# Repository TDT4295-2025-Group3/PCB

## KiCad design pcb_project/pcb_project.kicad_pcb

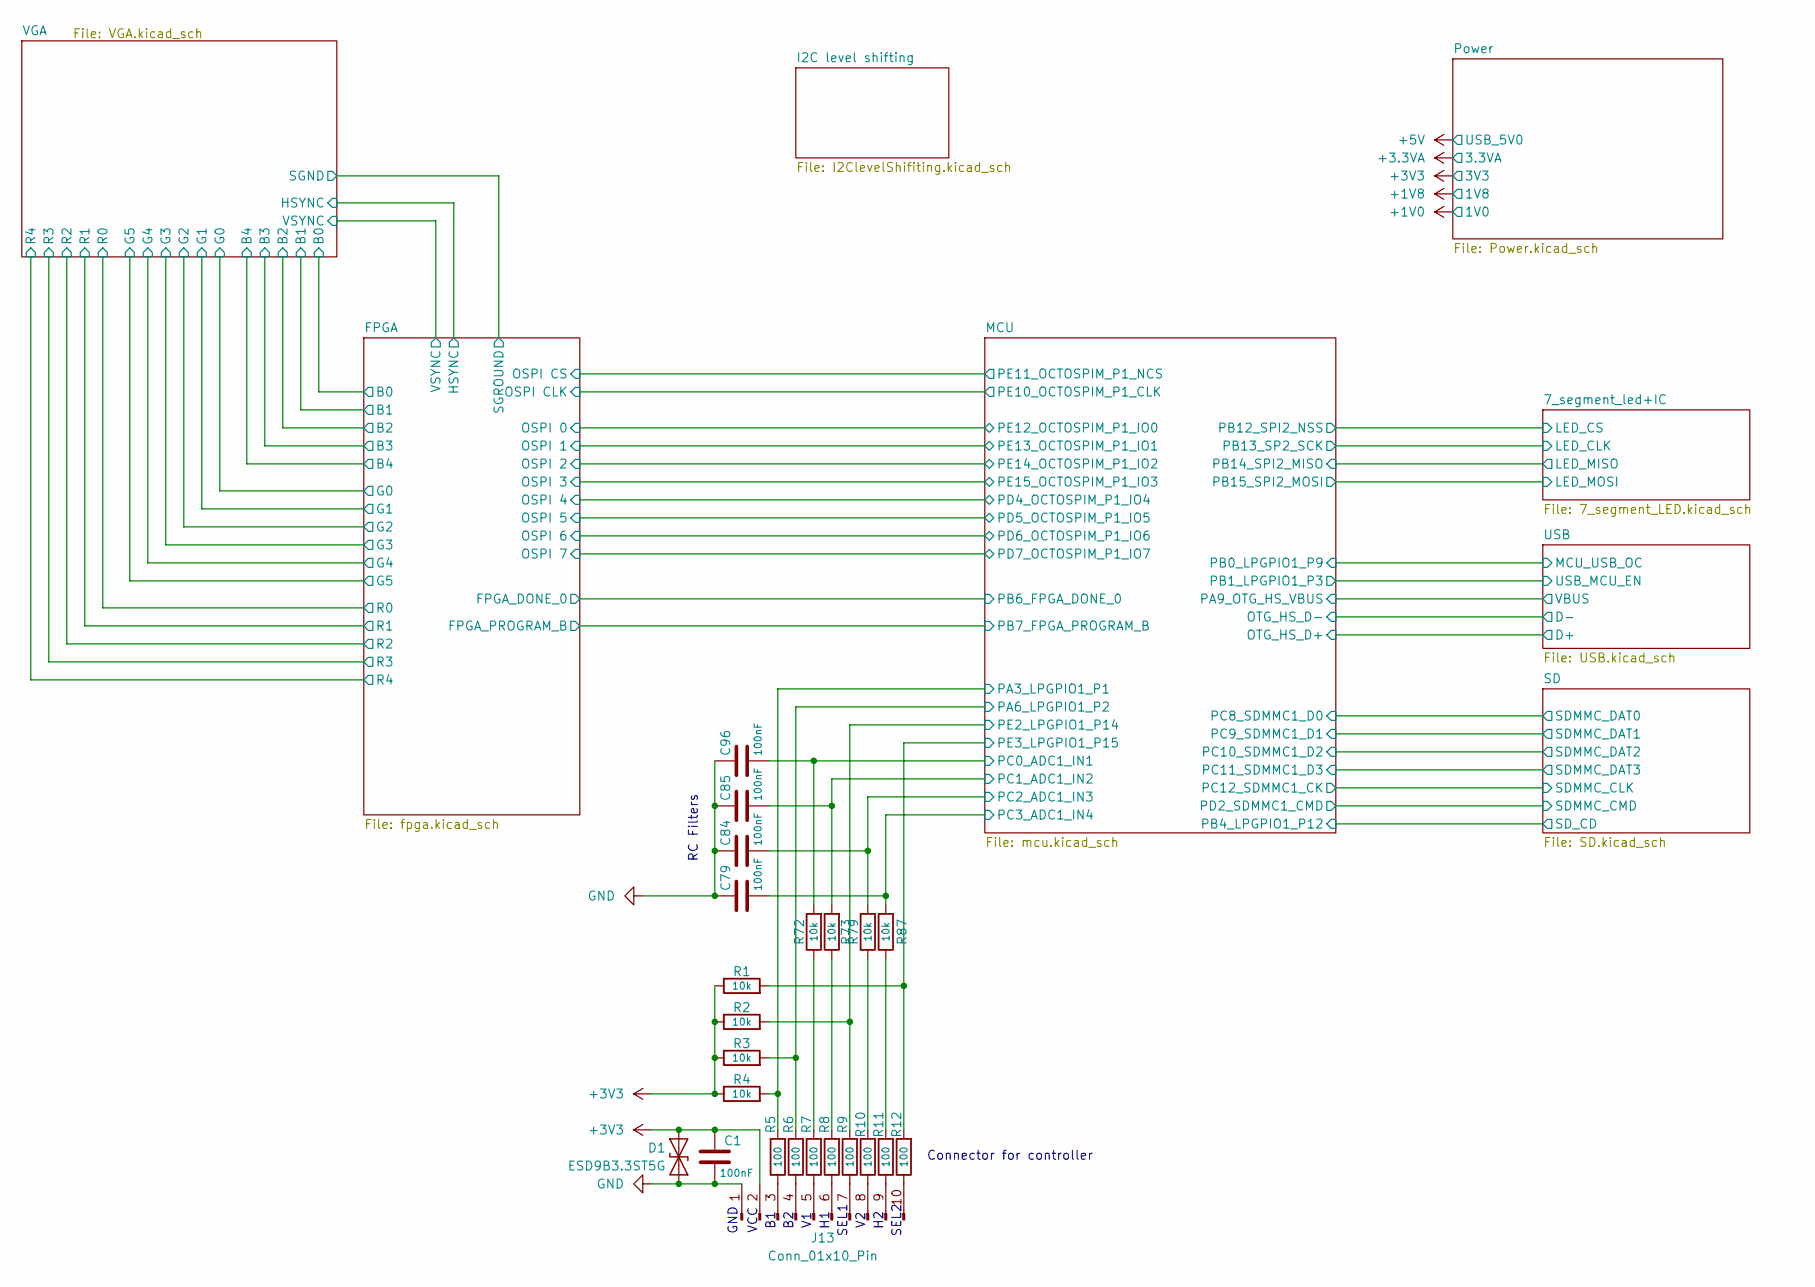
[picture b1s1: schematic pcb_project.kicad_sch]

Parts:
C1, C79, C84, C85, C96: 100nF; C_0603_1608Metric_Pad1.08x0.95mm_HandSolder
D1: ESD9B3.3ST5G; D_SOD-923
J13: Conn_01x10_Pin; PinHeader_1x10_P2.54mm_Vertical
R1, R2, R3, R4, R72, R73, R79, R87: 10k; R_0805_2012Metric_Pad1.20x1.40mm_HandSolder
R5, R6, R7, R8, R9, R10, R11, R12: 100; R_0805_2012Metric_Pad1.20x1.40mm_HandSolder

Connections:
+3V3: C1.1, D1.1 (A1), J13.2, R1.1, R2.1, R3.1, R4.1; also elsewhere on the board
/MCU/PA3_LPGPIO1_P1: R4.2, R5.2; also elsewhere on the board
/MCU/PA6_LPGPIO1_P2: R3.2, R6.2; also elsewhere on the board
/MCU/PC0_ADC1_IN1: C96.2, R72.2; also elsewhere on the board
/MCU/PC1_ADC1_IN2: C85.2, R73.2; also elsewhere on the board
/MCU/PC2_ADC1_IN3: C84.2, R79.2; also elsewhere on the board
/MCU/PC3_ADC1_IN4: C79.2, R87.2; also elsewhere on the board
/MCU/PE2_LPGPIO1_P14: R2.2, R9.2; also elsewhere on the board
/MCU/PE3_LPGPIO1_P15: R1.2, R12.2; also elsewhere on the board
GND: C1.2, C79.1, C84.1, C85.1, C96.1, D1.2 (A2), J13.1; also elsewhere on the board
unnamed: J13.3, R5.1
unnamed: J13.4, R6.1
unnamed: J13.5, R7.1
unnamed: J13.6, R8.1
unnamed: J13.7, R9.1
unnamed: J13.8, R10.1
unnamed: J13.9, R11.1
unnamed: J13.10, R12.1
unnamed: R7.2, R72.1
unnamed: R10.2, R79.1
unnamed: R11.2, R87.1
unnamed: R8.2, R73.1

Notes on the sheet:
VCC
SEL1
SEL2
Connector for controller
RC Filters
GND

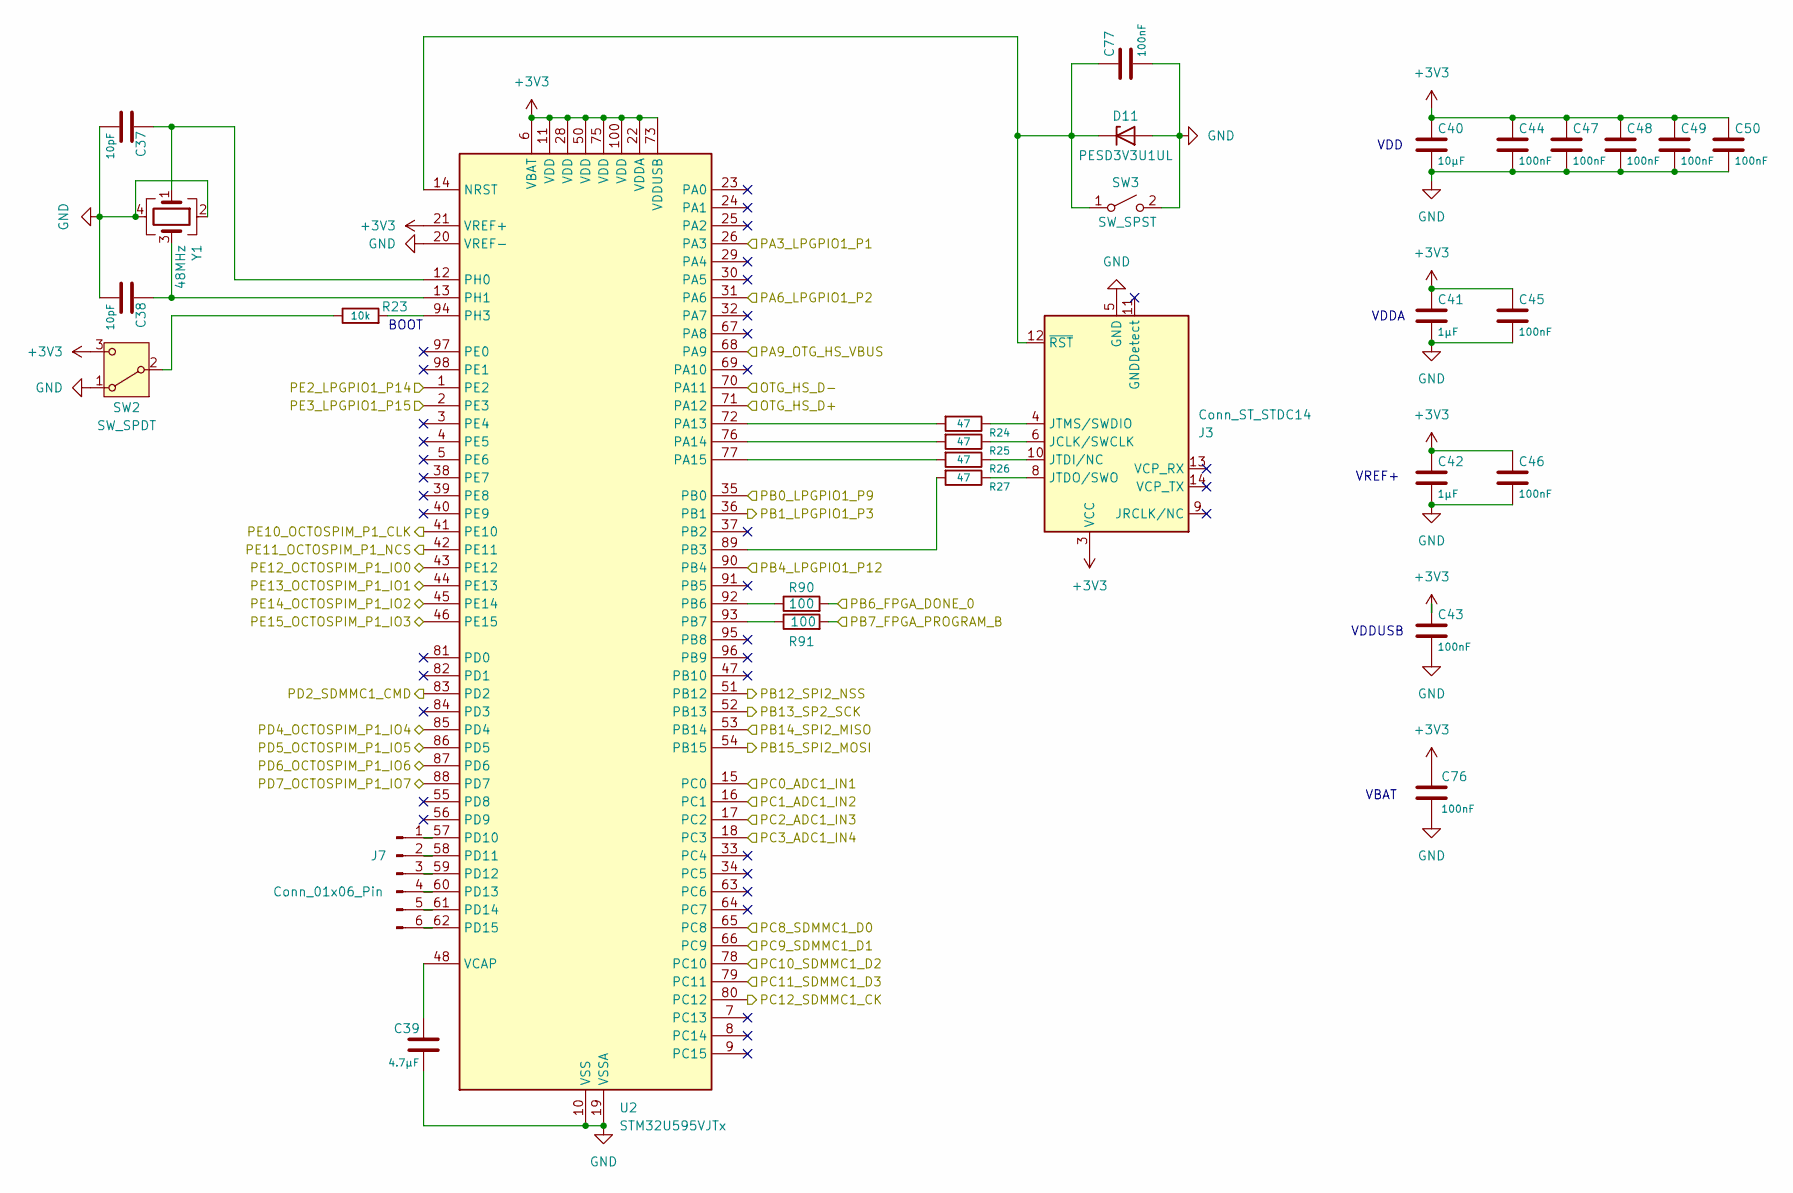
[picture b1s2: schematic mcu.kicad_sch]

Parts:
C37, C38: 10pF; C_0603_1608Metric_Pad1.08x0.95mm_HandSolder
C39: 4.7μF; C_0805_2012Metric_Pad1.18x1.45mm_HandSolder
C40: 10μF; C_1206_3216Metric_Pad1.33x1.80mm_HandSolder
C41, C42: 1μF; C_0805_2012Metric_Pad1.18x1.45mm_HandSolder
C43, C44, C45, C46, C47, C48, C49, C50, C76, C77: 100nF; C_0603_1608Metric_Pad1.08x0.95mm_HandSolder
D11: PESD3V3U1UL; D_SOD-882
J3: Conn_ST_STDC14; PinHeader_2x07_P1.27mm_Vertical
J7: Conn_01x06_Pin; PinHeader_1x06_P2.54mm_Vertical
R23: 10k; R_0805_2012Metric_Pad1.20x1.40mm_HandSolder
R24, R25, R26, R27: 47; R_0805_2012Metric_Pad1.20x1.40mm_HandSolder
R90, R91: 100; R_0805_2012Metric_Pad1.20x1.40mm_HandSolder
SW2: SW_SPDT; SW_Slide_SPDT_Straight_CK_OS102011MS2Q
SW3: SW_SPST; SW_TH_Tactile_Omron_B3F-100x
U2: STM32U595VJTx; LQFP-100_14x14mm_P0.5mm
Y1: 48MHz; OSCCC320X250X60N

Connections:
+3V3: C40.1, C41.1, C42.1, C43.1, C44.1, C45.1, C46.1, C47.1, C48.1, C49.1, C50.1, C76.1, J3.3 (VCC), SW2.3 (C), U2.6 (VBAT), U2.11 (VDD), U2.21 (VREF+), U2.22 (VDDA), U2.28 (VDD), U2.50 (VDD), U2.73 (VDDUSB), U2.75 (VDD), U2.100 (VDD); also elsewhere on the board
/7_segment_led+IC/LED_CLK: U2.52 (PB13); also elsewhere on the board
/7_segment_led+IC/LED_CS: U2.51 (PB12); also elsewhere on the board
/7_segment_led+IC/LED_MISO: U2.53 (PB14); also elsewhere on the board
/7_segment_led+IC/LED_MOSI: U2.54 (PB15); also elsewhere on the board
/FPGA/FPGA_DONE_0: R90.2; also elsewhere on the board
/FPGA/FPGA_PROGRAM_B: R91.2; also elsewhere on the board
/FPGA/OSPI 0: U2.43 (PE12); also elsewhere on the board
/FPGA/OSPI 1: U2.44 (PE13); also elsewhere on the board
/FPGA/OSPI 2: U2.45 (PE14); also elsewhere on the board
/FPGA/OSPI 3: U2.46 (PE15); also elsewhere on the board
/FPGA/OSPI 4: U2.85 (PD4); also elsewhere on the board
/FPGA/OSPI 5: U2.86 (PD5); also elsewhere on the board
/FPGA/OSPI 6: U2.87 (PD6); also elsewhere on the board
/FPGA/OSPI 7: U2.88 (PD7); also elsewhere on the board
/FPGA/OSPI CLK: U2.41 (PE10); also elsewhere on the board
/FPGA/OSPI CS: U2.42 (PE11); also elsewhere on the board
/MCU/OTG_HS_D+: U2.71 (PA12); also elsewhere on the board
/MCU/OTG_HS_D-: U2.70 (PA11); also elsewhere on the board
/MCU/PA3_LPGPIO1_P1: U2.26 (PA3); also elsewhere on the board
/MCU/PA6_LPGPIO1_P2: U2.31 (PA6); also elsewhere on the board
/MCU/PA9_OTG_HS_VBUS: U2.68 (PA9); also elsewhere on the board
/MCU/PB0_LPGPIO1_P9: U2.35 (PB0); also elsewhere on the board
/MCU/PB1_LPGPIO1_P3: U2.36 (PB1); also elsewhere on the board
/MCU/PB4_LPGPIO1_P12: U2.90 (PB4); also elsewhere on the board
/MCU/PC0_ADC1_IN1: U2.15 (PC0); also elsewhere on the board
/MCU/PC1_ADC1_IN2: U2.16 (PC1); also elsewhere on the board
/MCU/PC2_ADC1_IN3: U2.17 (PC2); also elsewhere on the board
/MCU/PC3_ADC1_IN4: U2.18 (PC3); also elsewhere on the board
/MCU/PC8_SDMMC1_D0: U2.65 (PC8); also elsewhere on the board
/MCU/PC9_SDMMC1_D1: U2.66 (PC9); also elsewhere on the board
/MCU/PC10_SDMMC1_D2: U2.78 (PC10); also elsewhere on the board
/MCU/PC11_SDMMC1_D3: U2.79 (PC11); also elsewhere on the board
/MCU/PC12_SDMMC1_CK: U2.80 (PC12); also elsewhere on the board
/MCU/PD2_SDMMC1_CMD: U2.83 (PD2); also elsewhere on the board
/MCU/PE2_LPGPIO1_P14: U2.1 (PE2); also elsewhere on the board
/MCU/PE3_LPGPIO1_P15: U2.2 (PE3); also elsewhere on the board
GND: C37.2, C38.2, C39.2, C40.2, C41.2, C42.2, C43.2, C44.2, C45.2, C46.2, C47.2, C48.2, C49.2, C50.2, C76.2, C77.2, D11.2 (A), J3.5 (GND), J3.7 (GND), SW2.1 (A), SW3.2 (B), U2.10 (VSS), U2.19 (VSSA), U2.20 (VREF-), U2.27 (VSS), U2.49 (VSS), U2.74 (VSS), U2.99 (VSS), Y1.2, Y1.4; also elsewhere on the board
unnamed: C77.1, D11.1 (K), J3.12 (~RST), SW3.1 (A), U2.14 (NRST)
unnamed: J3.6 (JCLK/SWCLK), R25.1
unnamed: J3.10 (JTDI/NC), R26.1
unnamed: J3.8 (JTDO/SWO), R27.1
unnamed: J3.4 (JTMS/SWDIO), R24.1
unnamed: J7.1, U2.57 (PD10)
unnamed: J7.2, U2.58 (PD11)
unnamed: J7.3, U2.59 (PD12)
unnamed: J7.4, U2.60 (PD13)
unnamed: J7.5, U2.61 (PD14)
unnamed: J7.6, U2.62 (PD15)
unnamed: R23.1, SW2.2 (B)
unnamed: R24.2, U2.72 (PA13)
unnamed: R25.2, U2.76 (PA14)
unnamed: R26.2, U2.77 (PA15)
unnamed: R27.2, U2.89 (PB3)
unnamed: R90.1, U2.92 (PB6)
unnamed: R91.1, U2.93 (PB7)
unnamed: C37.1, U2.12 (PH0), Y1.1
unnamed: C38.1, U2.13 (PH1), Y1.3
unnamed: R23.2, U2.94 (PH3)
unnamed: C39.1, U2.48 (VCAP)

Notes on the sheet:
VDD
BOOT
VDDA
VBAT
VDDUSB
VREF+

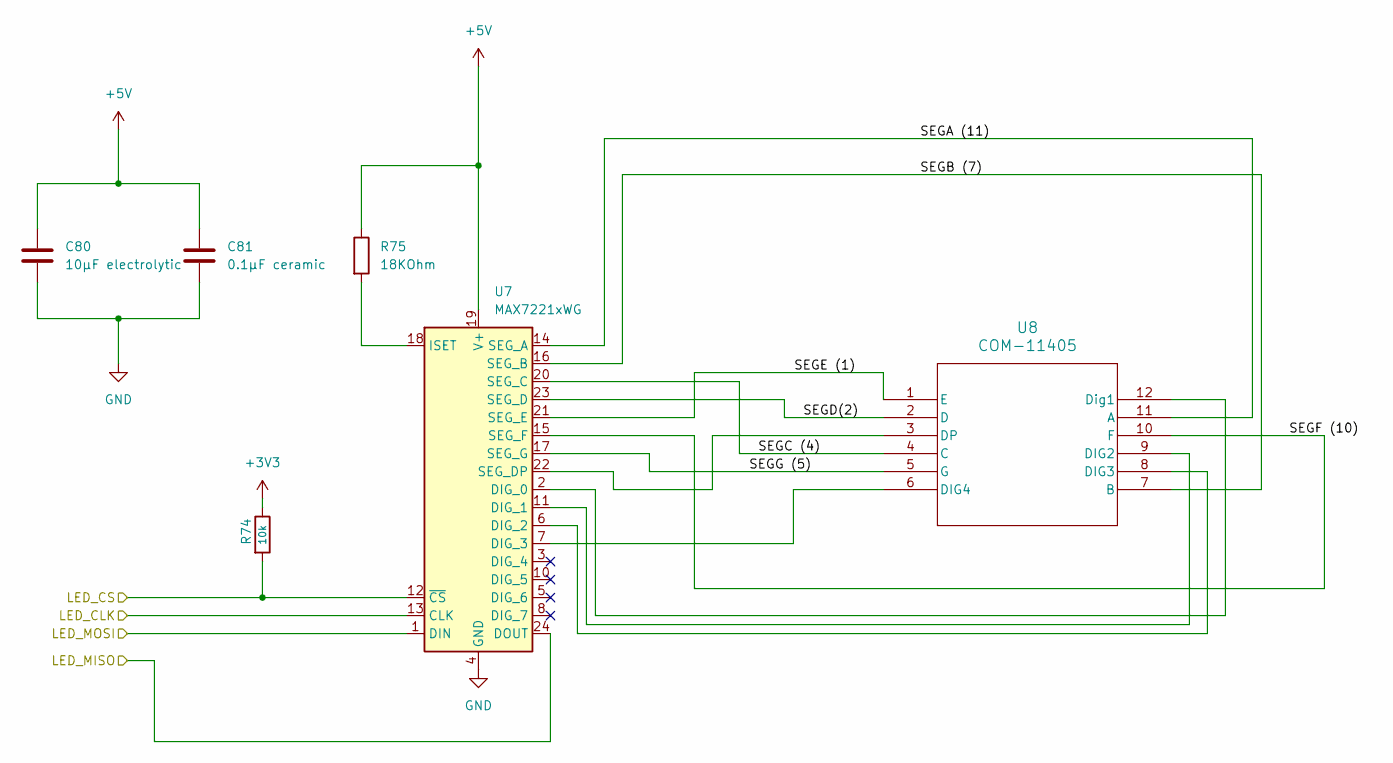
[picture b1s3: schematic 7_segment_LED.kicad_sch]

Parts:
C80: 10µF electrolytic; CP_Radial_D5.0mm_P2.00mm
C81: 0.1µF ceramic; C_0603_1608Metric_Pad1.08x0.95mm_HandSolder
R74: 10k; R_0805_2012Metric_Pad1.20x1.40mm_HandSolder
R75: 18KOhm; R_0805_2012Metric_Pad1.20x1.40mm_HandSolder
U7: MAX7221xWG; SOIC-24W_7.5x15.4mm_P1.27mm
U8: COM-11405; COM-11405_SPK

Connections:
+3V3: R74.1; also elsewhere on the board
+5V: C80.1, C81.1, R75.1, U7.19 (V+); also elsewhere on the board
/7_segment_led+IC/LED_CLK: U7.13 (CLK); also elsewhere on the board
/7_segment_led+IC/LED_CS: R74.2, U7.12 (~CS); also elsewhere on the board
/7_segment_led+IC/LED_MISO: U7.24 (DOUT); also elsewhere on the board
/7_segment_led+IC/LED_MOSI: U7.1 (DIN); also elsewhere on the board
/7_segment_led+IC/SEGA (11): U7.14 (SEG_A), U8.11 (A)
/7_segment_led+IC/SEGB (7): U7.16 (SEG_B), U8.7 (B)
/7_segment_led+IC/SEGC (4): U7.20 (SEG_C), U8.4 (C)
/7_segment_led+IC/SEGD(2): U7.23 (SEG_D), U8.2 (D)
/7_segment_led+IC/SEGE (1): U7.21 (SEG_E), U8.1 (E)
/7_segment_led+IC/SEGF (10): U7.15 (SEG_F), U8.10 (F)
/7_segment_led+IC/SEGG (5): U7.17 (SEG_G), U8.5 (G)
GND: C80.2, C81.2, U7.4 (GND), U7.9 (GND); also elsewhere on the board
unnamed: U7.2 (DIG_0), U8.12 (Dig1)
unnamed: U7.11 (DIG_1), U8.9 (DIG2)
unnamed: U7.6 (DIG_2), U8.8 (DIG3)
unnamed: U7.7 (DIG_3), U8.6 (DIG4)
unnamed: R75.2, U7.18 (ISET)
unnamed: U7.22 (SEG_DP), U8.3 (DP)

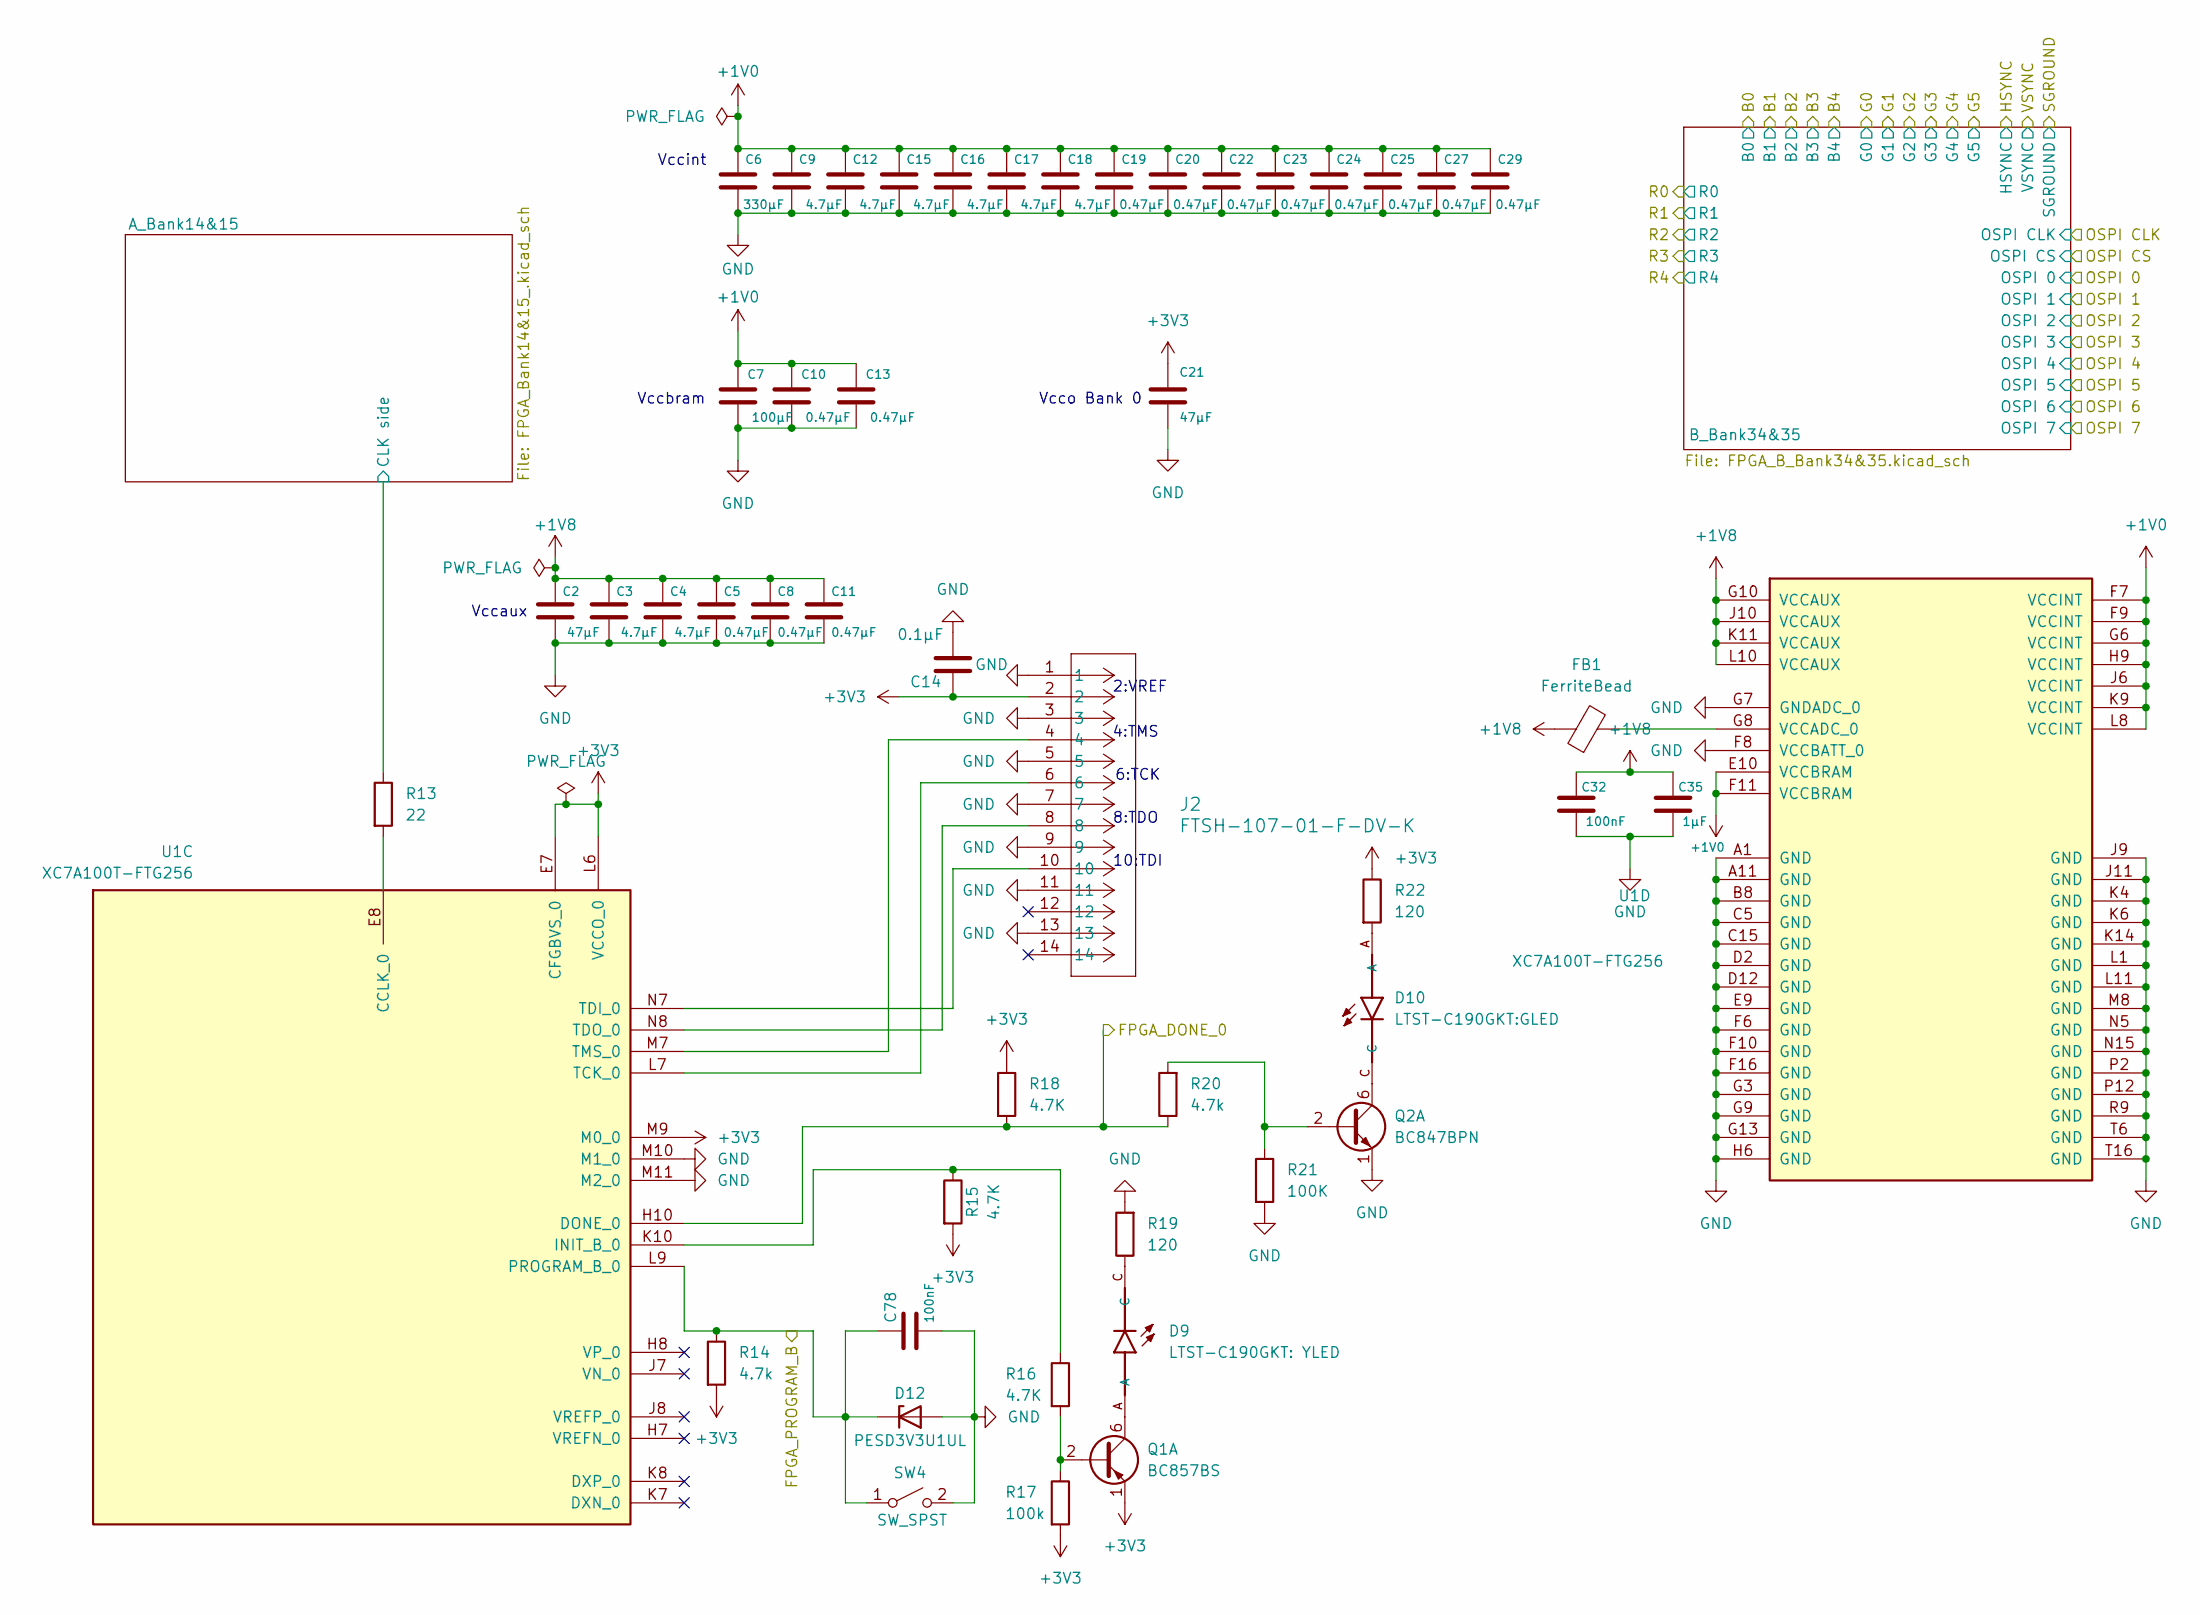
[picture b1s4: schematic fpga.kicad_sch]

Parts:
C2, C21: 47µF; C_1210_3225Metric_Pad1.33x2.70mm_HandSolder
C3, C4, C9, C12, C15, C16, C17, C18: 4.7µF; C_0603_1608Metric_Pad1.08x0.95mm_HandSolder
C5, C8, C10, C11, C13, C19, C20, C22, C23, C24, C25, C27, C29: 0.47µF; C_0603_1608Metric_Pad1.08x0.95mm_HandSolder
C6: 330µF; CP_EIA-7343-31_Kemet-D_HandSolder
C7: 100µF; C_1210_3225Metric_Pad1.33x2.70mm_HandSolder
C14: 0.1µF; C_0603_1608Metric_Pad1.08x0.95mm_HandSolder
C32, C78: 100nF; C_0603_1608Metric_Pad1.08x0.95mm_HandSolder
C35: 1µF; C_0603_1608Metric_Pad1.08x0.95mm_HandSolder
D9: LTST-C190GKT: YLED; LEDM1608X80
D10: LTST-C190GKT:GLED; LEDM1608X80
D12: PESD3V3U1UL; D_SOD-882
FB1: FerriteBead; L_0805_2012Metric_Pad1.15x1.40mm_HandSolder
J2: FTSH-107-01-F-DV-K; CON14_2X7_DUK_FTSH_SAI
Q1: BC857BS; SOT-363_SC-70-6
Q2: BC847BPN; SOT-363_SC-70-6
R13: 22; R_0805_2012Metric_Pad1.20x1.40mm_HandSolder
R14, R20: 4.7k; R_0805_2012Metric_Pad1.20x1.40mm_HandSolder
R15, R16, R18: 4.7K; R_0805_2012Metric_Pad1.20x1.40mm_HandSolder
R17: 100k; R_0805_2012Metric_Pad1.20x1.40mm_HandSolder
R19, R22: 120; R_0805_2012Metric_Pad1.20x1.40mm_HandSolder
R21: 100K; R_0805_2012Metric_Pad1.20x1.40mm_HandSolder
SW4: SW_SPST; SW_TH_Tactile_Omron_B3F-100x
U1: XC7A100T-FTG256; Xilinx_FTG256

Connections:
+1V0: C6.1, C7.1, C9.1, C10.1, C12.1, C13.1, C15.1, C16.1, C17.1, C18.1, C19.1, C20.1, C22.1, C23.1, C24.1, C25.1, C27.1, C29.1, U1.E10 (VCCBRAM), U1.F7 (VCCINT), U1.F9 (VCCINT), U1.F11 (VCCBRAM), U1.G6 (VCCINT), U1.H9 (VCCINT), U1.J6 (VCCINT), U1.K9 (VCCINT), U1.L8 (VCCINT); also elsewhere on the board
+1V8: C2.1, C3.1, C4.1, C5.1, C8.1, C11.1, C32.1, C35.1, FB1.1, U1.G10 (VCCAUX), U1.J10 (VCCAUX), U1.K11 (VCCAUX), U1.L10 (VCCAUX); also elsewhere on the board
+3V3: C14.1, C21.1, J2.2, Q1.1 (E1), R14.2, R15.2, R17.2, R18.1, R22.1, U1.E7 (CFGBVS_0), U1.L6 (VCCO_0), U1.M9 (M0_0); also elsewhere on the board
/FPGA/A_Bank14&15/CLK side: R13.1; also elsewhere on the board
/FPGA/FPGA_DONE_0: R18.2, R20.1, U1.H10 (DONE_0); also elsewhere on the board
/FPGA/FPGA_PROGRAM_B: C78.1, D12.1 (K), R14.1, SW4.1 (A), U1.L9 (PROGRAM_B_0); also elsewhere on the board
GND: C2.2, C3.2, C4.2, C5.2, C6.2, C7.2, C8.2, C9.2, C10.2, C11.2, C12.2, C13.2, C14.2, C15.2, C16.2, C17.2, C18.2, C19.2, C20.2, C21.2, C22.2, C23.2, C24.2, C25.2, C27.2, C29.2, C32.2, C35.2, C78.2, D12.2 (A), J2.1, J2.3, J2.5, J2.7, J2.9, J2.11, J2.13, Q2.1 (E1), R19.2, R21.2, SW4.2 (B), U1.A1 (GND), U1.A11 (GND), U1.B8 (GND), U1.C5 (GND), U1.C15 (GND), U1.D2 (GND), U1.D12 (GND), U1.E9 (GND), U1.F6 (GND), U1.F8 (VCCBATT_0), U1.F10 (GND), U1.F16 (GND), U1.G3 (GND), U1.G7 (GNDADC_0), U1.G9 (GND), U1.G13 (GND), U1.H6 (GND), U1.J9 (GND), U1.J11 (GND), U1.K4 (GND), U1.K6 (GND), U1.K14 (GND), U1.L1 (GND), U1.L11 (GND), U1.M8 (GND), U1.M10 (M1_0), U1.M11 (M2_0), U1.N5 (GND), U1.N15 (GND), U1.P2 (GND), U1.P12 (GND), U1.R9 (GND), U1.T6 (GND), U1.T16 (GND); also elsewhere on the board
unnamed: D9.C, R19.1
unnamed: D10.A, R22.2
unnamed: Q1.2 (B1), R16.2, R17.1
unnamed: D9.A, Q1.6 (C1)
unnamed: Q2.2 (B1), R20.2, R21.1
unnamed: D10.C, Q2.6 (C1)
unnamed: R13.2, U1.E8 (CCLK_0)
unnamed: R15.1, R16.1, U1.K10 (INIT_B_0)
unnamed: J2.6, U1.L7 (TCK_0)
unnamed: J2.10, U1.N7 (TDI_0)
unnamed: J2.8, U1.N8 (TDO_0)
unnamed: J2.4, U1.M7 (TMS_0)
unnamed: FB1.2, U1.G8 (VCCADC_0)

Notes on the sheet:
8:TDO
Vccaux
6:TCK
10:TDI
Vcco Bank 0
4:TMS
2:VREF
Vccint
Vccbram

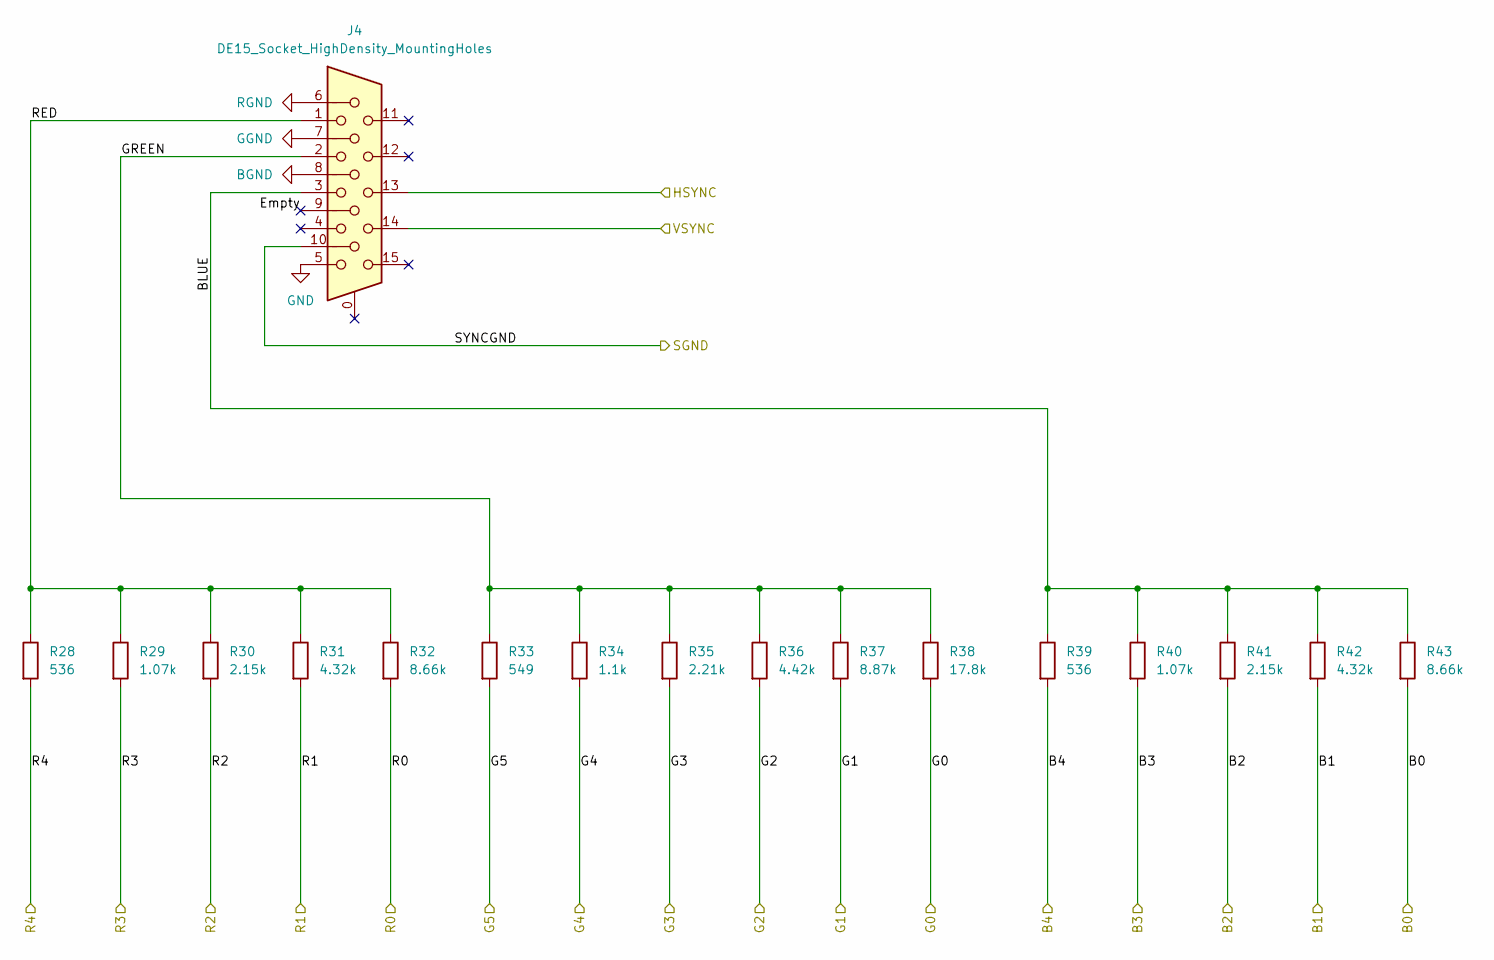
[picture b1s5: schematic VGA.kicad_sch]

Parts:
J4: DE15_Socket_HighDensity_MountingHoles; CONN_L77HDE15SD1CH4F_AMP
R28, R39: 536; R_0805_2012Metric_Pad1.20x1.40mm_HandSolder
R29, R40: 1.07k; R_0805_2012Metric_Pad1.20x1.40mm_HandSolder
R30, R41: 2.15k; R_0805_2012Metric_Pad1.20x1.40mm_HandSolder
R31, R42: 4.32k; R_0805_2012Metric_Pad1.20x1.40mm_HandSolder
R32, R43: 8.66k; R_0805_2012Metric_Pad1.20x1.40mm_HandSolder
R33: 549; R_0805_2012Metric_Pad1.20x1.40mm_HandSolder
R34: 1.1k; R_0805_2012Metric_Pad1.20x1.40mm_HandSolder
R35: 2.21k; R_0805_2012Metric_Pad1.20x1.40mm_HandSolder
R36: 4.42k; R_0805_2012Metric_Pad1.20x1.40mm_HandSolder
R37: 8.87k; R_0805_2012Metric_Pad1.20x1.40mm_HandSolder
R38: 17.8k; R_0805_2012Metric_Pad1.20x1.40mm_HandSolder

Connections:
/FPGA/HSYNC: J4.13; also elsewhere on the board
/FPGA/VSYNC: J4.14; also elsewhere on the board
/VGA/B0: R43.2; also elsewhere on the board
/VGA/B1: R42.2; also elsewhere on the board
/VGA/B2: R41.2; also elsewhere on the board
/VGA/B3: R40.2; also elsewhere on the board
/VGA/B4: R39.2; also elsewhere on the board
/VGA/BLUE: J4.3, R39.1, R40.1, R41.1, R42.1, R43.1
/VGA/Empty: J4.9
/VGA/G0: R38.2; also elsewhere on the board
/VGA/G1: R37.2; also elsewhere on the board
/VGA/G2: R36.2; also elsewhere on the board
/VGA/G3: R35.2; also elsewhere on the board
/VGA/G4: R34.2; also elsewhere on the board
/VGA/G5: R33.2; also elsewhere on the board
/VGA/GREEN: J4.2, R33.1, R34.1, R35.1, R36.1, R37.1, R38.1
/VGA/R0: R32.2; also elsewhere on the board
/VGA/R1: R31.2; also elsewhere on the board
/VGA/R2: R30.2; also elsewhere on the board
/VGA/R3: R29.2; also elsewhere on the board
/VGA/R4: R28.2; also elsewhere on the board
/VGA/RED: J4.1, R28.1, R29.1, R30.1, R31.1, R32.1
BGND: J4.8
GGND: J4.7
GND: J4.5, J4.10; also elsewhere on the board
RGND: J4.6

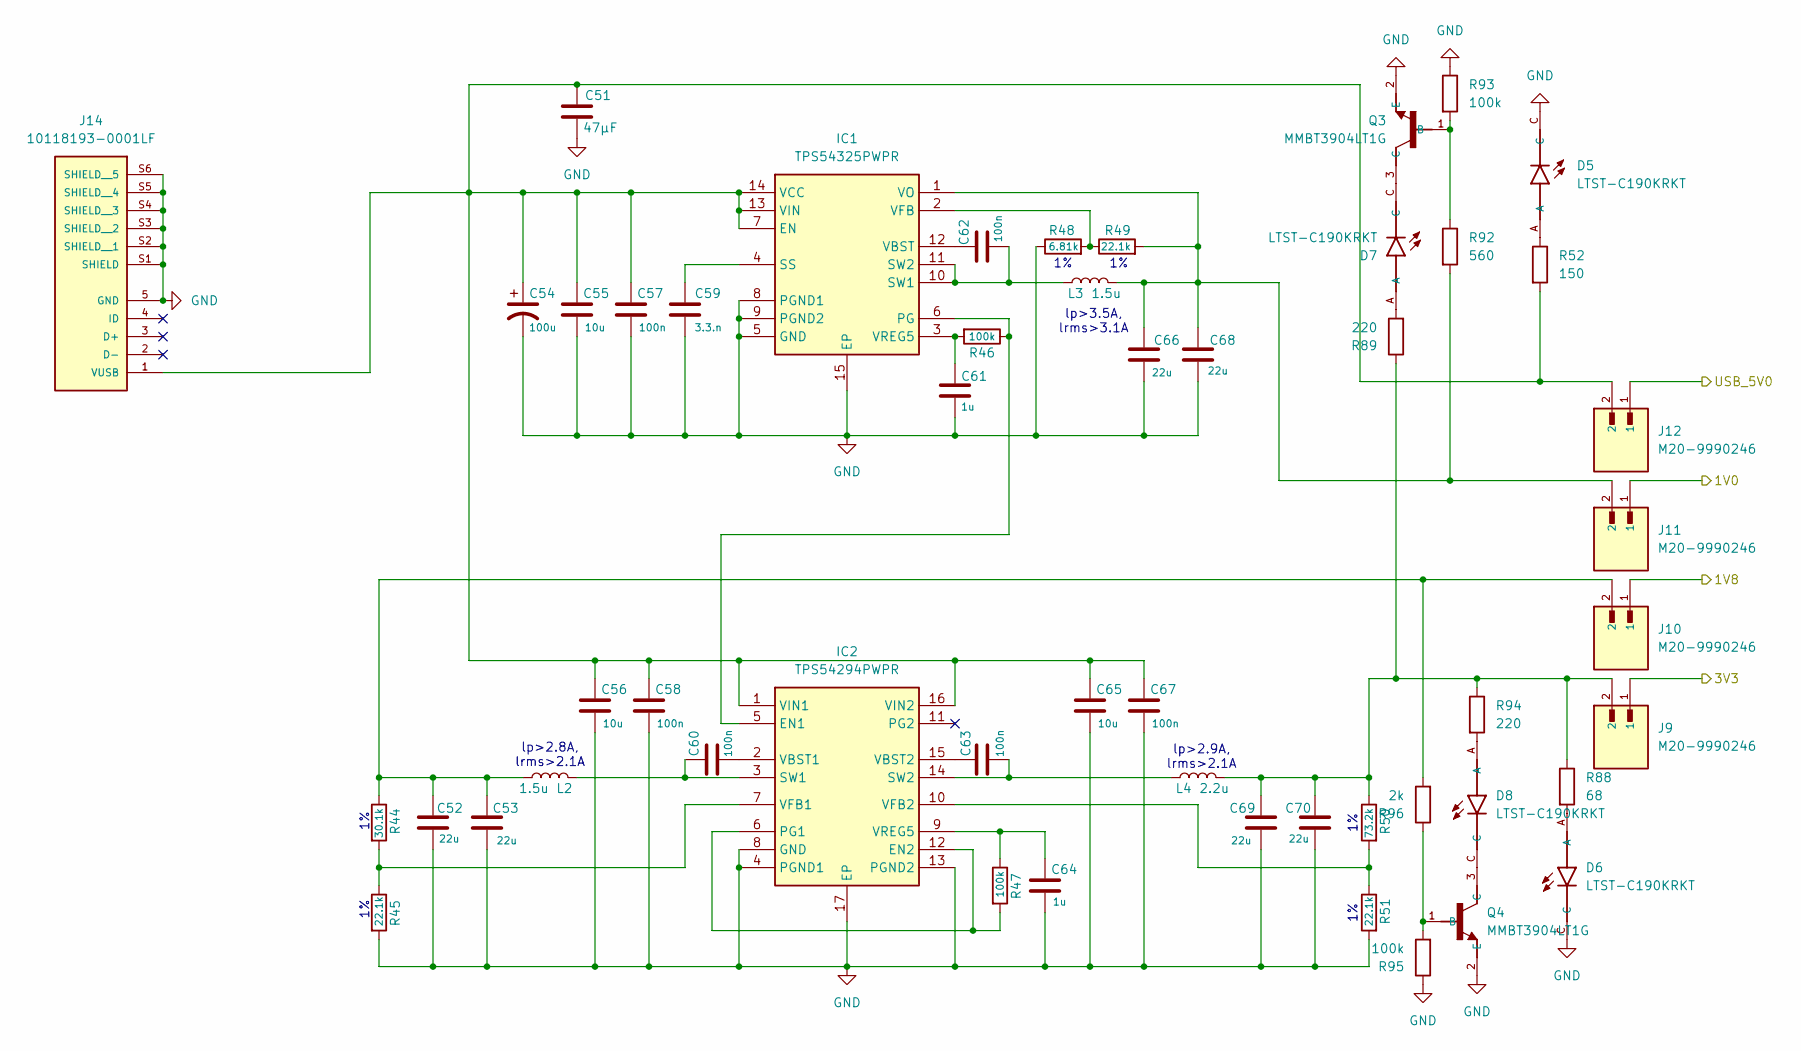
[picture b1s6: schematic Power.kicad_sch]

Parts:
C51: 47μF; C_1210_3225Metric_Pad1.33x2.70mm_HandSolder
C52, C53, C66, C68, C69, C70: 22u; C_1206_3216Metric_Pad1.33x1.80mm_HandSolder
C54: 100u; C_1210_3225Metric_Pad1.33x2.70mm_HandSolder
C55, C56, C65: 10u; C_1206_3216Metric_Pad1.33x1.80mm_HandSolder
C57, C58, C60, C62, C63, C67: 100n; C_0603_1608Metric_Pad1.08x0.95mm_HandSolder
C59: 3.3.n; C_0603_1608Metric_Pad1.08x0.95mm_HandSolder
C61, C64: 1u; C_0805_2012Metric_Pad1.18x1.45mm_HandSolder
D5, D6, D7, D8: LTST-C190KRKT; LEDC1608X35N
IC1: TPS54325PWPR; SOP65P640X120-15N; Mouser Part Number 595-TPS54325PWPR
IC2: TPS54294PWPR; SOP65P640X120-17N; Mouser Part Number 595-TPS54294PWPR
J9, J10, J11, J12: M20-9990246; HARWIN_M20-9990246; PARTREV 14
J14: 10118193-0001LF; AMPHENOL_10118193-0001LF; PARTREV E
L2, L3: 1.5u; L_Bourns_SRP5030T
L4: 2.2u; L_Bourns-SRN4018
Q3, Q4: MMBT3904LT1G; SOT95P240X111-3N
R44: 30.1k; R_0805_2012Metric_Pad1.20x1.40mm_HandSolder
R45, R49, R51: 22.1k; R_0805_2012Metric_Pad1.20x1.40mm_HandSolder
R46, R47, R93, R95: 100k; R_0805_2012Metric_Pad1.20x1.40mm_HandSolder
R48: 6.81k; R_0805_2012Metric_Pad1.20x1.40mm_HandSolder
R50: 73.2k; R_0805_2012Metric_Pad1.20x1.40mm_HandSolder
R52: 150; R_0805_2012Metric_Pad1.20x1.40mm_HandSolder
R88: 68; R_0805_2012Metric_Pad1.20x1.40mm_HandSolder
R89, R94: 220; R_0805_2012Metric_Pad1.20x1.40mm_HandSolder
R92: 560; R_0805_2012Metric_Pad1.20x1.40mm_HandSolder
R96: 2k; R_0805_2012Metric_Pad1.20x1.40mm_HandSolder

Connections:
+1V0: J11.1; also elsewhere on the board
+1V8: J10.1; also elsewhere on the board
+3V3: J9.1; also elsewhere on the board
+5V: J12.1; also elsewhere on the board
GND: C51.2, C52.2, C53.2, C54.2, C55.2, C56.2, C57.2, C58.2, C59.2, C61.2, C64.2, C65.2, C66.2, C67.2, C68.2, C69.2, C70.2, D5.C, D6.C, IC1.5 (GND), IC1.8 (PGND1), IC1.9 (PGND2), IC1.15 (EP), IC2.4 (PGND1), IC2.8 (GND), IC2.13 (PGND2), IC2.17 (EP), J14.5 (GND), J14.S1 (SHIELD), J14.S2 (SHIELD__1), J14.S3 (SHIELD__2), J14.S4 (SHIELD__3), J14.S5 (SHIELD__4), J14.S6 (SHIELD__5), Q3.2 (E), Q4.2 (E), R45.2, R48.1, R51.2, R93.1, R95.1; also elsewhere on the board
unnamed: C52.1, C53.1, J10.2, L2.2, R44.1, R96.2
unnamed: C69.1, C70.1, J9.2, L4.2, R50.1, R88.1, R89.1, R94.1
unnamed: D5.A, R52.1
unnamed: D6.A, R88.2
unnamed: D7.A, R89.2
unnamed: D8.A, R94.2
unnamed: C51.1, C54.1, C55.1, C56.1, C57.1, C58.1, C65.1, C67.1, IC1.7 (EN), IC1.13 (VIN), IC1.14 (VCC), IC2.1 (VIN1), IC2.16 (VIN2), J12.2, J14.1 (VUSB), R52.2
unnamed: IC1.6 (PG), IC2.5 (EN1), R46.1
unnamed: C59.1, IC1.4 (SS)
unnamed: C62.2, IC1.10 (SW1), IC1.11 (SW2), L3.1
unnamed: C62.1, IC1.12 (VBST)
unnamed: IC1.2 (VFB), R48.2, R49.1
unnamed: C66.1, C68.1, IC1.1 (VO), J11.2, L3.2, R49.2, R92.2
unnamed: C61.1, IC1.3 (VREG5), R46.2
unnamed: IC2.6 (PG1), IC2.12 (EN2), R47.2
unnamed: C60.2, IC2.3 (SW1), L2.1
unnamed: C63.2, IC2.14 (SW2), L4.1
unnamed: C60.1, IC2.2 (VBST1)
unnamed: C63.1, IC2.15 (VBST2)
unnamed: IC2.7 (VFB1), R44.2, R45.1
unnamed: IC2.10 (VFB2), R50.2, R51.1
unnamed: C64.1, IC2.9 (VREG5), R47.1
unnamed: Q3.1 (B), R92.1, R93.2
unnamed: D7.C, Q3.3 (C)
unnamed: Q4.1 (B), R95.2, R96.1
unnamed: D8.C, Q4.3 (C)

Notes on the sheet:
lp>2.8A, lrms>2.1A
lp>2.9A, lrms>2.1A
lp>3.5A, lrms>3.1A
